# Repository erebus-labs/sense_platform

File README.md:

sense-platform
==============
#Sensor Platform 
+ *Title:* A low-cost,  low-power sensor platform with modular sensor addition and base station reprogramming/configuration
+ *Project Short Name:* Open Sensor Platform
+ *Sponsors:* 
  + [Dr. Mike Borowczak](https://www.linkedin.com/in/mborowczak) @ [Erebus Labs](http://www.erebuslabs.com)
  + [Dr. Andrea Burrows] (http://uwyo.academia.edu/AndreaBurrows) @ [University of Wyoming](http://www.uwyo.edu/seced/faculty-staff/andrea-burrows.html)
+ *Senior Design Team:* 
    + Colten Nye
    + Steve Pierce
    + Golriz Sedaghat
+ *PSU Academic Advisor:* [Dr. Lisa Zurk](http://web.cecs.pdx.edu/~zurkl/) 
+ *Targeted Users:* K-20 students (and families/communities) who want to know about their environment 

## Problem/Task
Current sensor platforms are either completed closed source and expensive or partially open, non-customizable, and trivial. The task at hand is to build a fully contained sensor platform / collection device for $25-$50 USD for at volume runs (development versions would be higher with short PCB runs).  The sensor platform must include the ability to add both sensors (physical components) as well as custom code in an intuitive (GUI?) programming environment.

##Background
Current hardware sensor solutions either require programming/electronics experience beyond the reach of many K12 (K20) students, parents, teachers and faculty – or they so turn-key that there is little to no “STEM” required to get a solution up and running. Furthermore, there are currently no “build it yourself” approaches to sensor design. The closest existing solutions revolve around the Arduino platform – though the short coming here is again the abstraction of many of the details as well as the barrier of entry for most K12 students, parents, faculty – especially in mid-large scale deployments in a classroom or a school (>30-1000 units).

In 2013/2014 a first revision Proof of Concept was developed and implemented – this can be used as a starting point once preliminary design investigation has concluded.

##Skill Requirements (Order of importance):
+ embedded System Design {Architecture, Programming}
+ Platform Agnostic Program Development (e.g. crossplatform or web UI)
+ PCB Layout and Design
+	Communication (BT, Serial, wifi?) 

##Other Details: 
+	IP Ownership: Joint/”none”: The goal is to release an open hardware device and software; joint ownership of the original design, publicly available for reuse under similar attribution
+	Extension after End of Project: 50-100 parts run to distribute to high-needs schools as a mechanism to enhance/drive STEM as a college degree option.
+	Publication Opportunities: Conference and Journal Publication both in K20 Education, IEEE Spectrum, and/or others (joint ownership: ECE team and Sponsors) [resume/CV builder!]
+	No NDA required. 

##Requirements (Wish List): **THIS SECTION SHOULD BE REPLACED BY PSU TEAM BEFORE DESIGN START**

###Must Have
+ [ ]	Low hardware cost <$50 per unit
+ [ ]	Open Source Hardware Design & Board (can use “closed source” components: ASICs, uC, etc.)
  + [ ]	Must Have a Multi-Chip solution – e.g. no single SoC; split data store
+ [ ]	Open Software Repository (github)
+ [ ]	Built-in basic sensor array (Oxygen, VoC, Accelerometer) + Ability to add at least one sensor
+ [ ]	Power:
  + [ ]	Low power operation (3 month duty-cycle; minimum 12 measurements per hour +sync)
  + [ ] Built in power source / power pack
+ [ ]	External Device Tethering/Sync upon physical request
+ [ ] Parameterized data collection mechanism
  + [ ] Set sensor Upper and Lower Thresholds
  + [ ] Polling frequency
  + [ ] Measurement to Physical Value Translation (they’re not all linear)
+ [ ] Set of units for each team member and two sponsors

###Like to Have
+ [ ]	Hardware cost <$30 per unit
+ [ ]	High Humidity Operation
+ [ ]	Swappable, Muxable Sensor array +software support
+ [ ]	Power
  + [ ] Ultra-low power operation (6 month duty-cycle; minimum 12 measurements per hour +sync)
  + [ ] Built in rechargeable power source / power pack
+ [ ] Device Tethering/Sync through Bluetooth/wifi in-range
+ [ ] High Level API wrapper to control device functionality for novice programmers
+ [ ] Partnership building with a local K-12 school; Flexible options include teacher conversations, lesson development, and/or helping with a lesson stemming from this research
+ [ ] Set of units for each team member and two sponsors + 5 extra units

###Nice to Have
+ [ ] Hardware cost <$15 per unit
+ [ ] GUI based overlay for API suitable for use by K-8 students
+ [ ] Power
  + [ ] Extremely-low power operation (12 month duty-cycle; minimum 12 measurements per hour +sync)
  + [ ] Built in power source w/solar recharge
+ [ ] Set of units for each team member and two sponsors + 10 extra units (5 to sponsors; 5 to PSU)

##Milestones:

###Hardware Evaluation to satisfy given constraints 
+ [ ] Main System: Modification of existing Open Hardware Design to create part or creation of custom PCB?
+ [ ] Power System: Battery capacity + recharge + cycled usage + communication cost?
+ [ ] Communication mechanisms: Effective low cost communication and sync (without taxing power source)

###Implementation
+ [ ] Development of full hardware solution (can you detect VoCs > ~0.5 PPM)
+ [ ] Develop a [G]UI to [re]program and sync data to/from remote sensing board 
+ [ ] Development of power system
+ [ ] Development of communication system
+ [ ] Develop the Android/iOS/PC software for receiving sync data, database/cloud upload, visualization

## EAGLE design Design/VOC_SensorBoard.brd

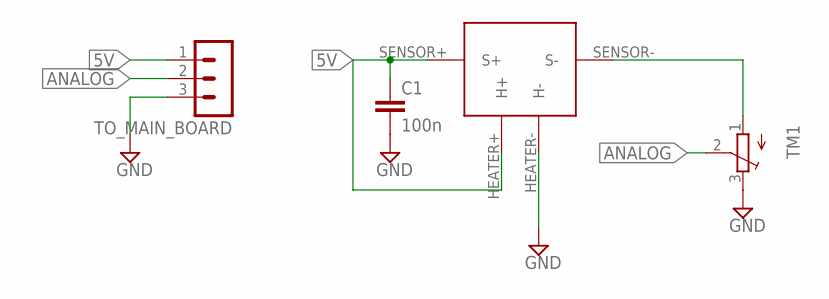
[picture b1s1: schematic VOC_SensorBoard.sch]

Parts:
C1: 100n; C0805
TM1: TRIMPOTTC33X; TC33X
TO_MAIN_BOARD: MA03-1
U$1: TGS2602

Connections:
5V: C1.1, TO_MAIN_BOARD.1, U$1.HEATER+ (H+), U$1.SENSOR+ (S+)
ANALOG: TM1.2 (S), TO_MAIN_BOARD.2
GND: C1.2, TM1.3 (E), TO_MAIN_BOARD.3, U$1.HEATER- (H-)
unnamed: TM1.1 (A), U$1.SENSOR- (S-)

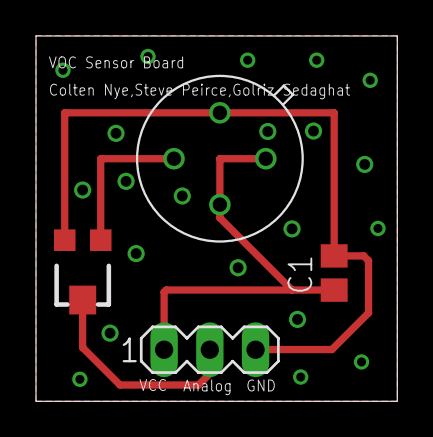
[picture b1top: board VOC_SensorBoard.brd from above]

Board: 2 copper layers, 20.1 x 20.3 mm, 4 parts (0 on the bottom side), 4 nets.

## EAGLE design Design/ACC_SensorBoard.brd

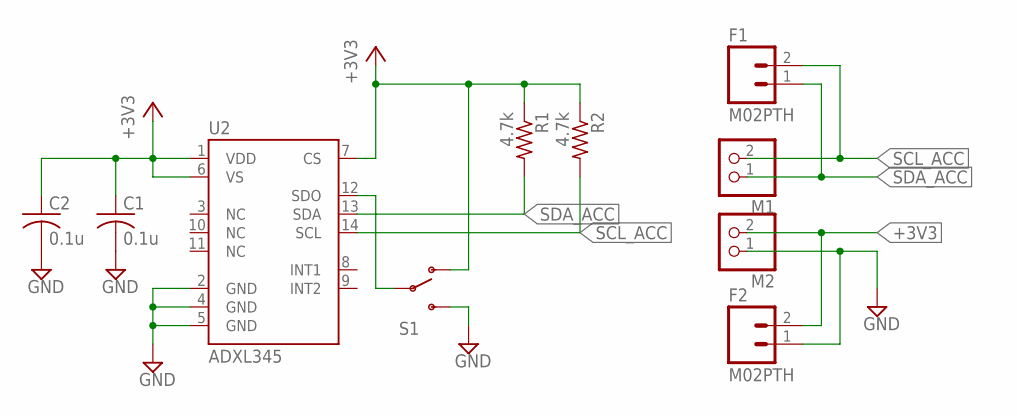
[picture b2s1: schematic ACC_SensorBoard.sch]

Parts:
C1, C2: 0.1u; C0805
F1, F2: M02PTH; 1X02
M1, M2: PINHD-1X2; 1X02
R1, R2: 4.7k; R0805
S1: SWITCH-SPDTSMD; AYZ0202
U2: ADXL345; LGA14

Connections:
+3V3: C1.1, C2.1, F2.2, M2.2, R1.1, R2.1, S1.1 (O), U2.1 (VDD), U2.6 (VS), U2.7 (CS)
GND: C1.2, C2.2, F2.1, M2.1, S1.3 (S), U2.2 (GND), U2.4 (GND), U2.5 (GND)
unnamed: S1.2, U2.12 (SDO)
SCL_ACC: F1.2, M1.2, R2.2, U2.14 (SCL)
SDA_ACC: F1.1, M1.1, R1.2, U2.13 (SDA)

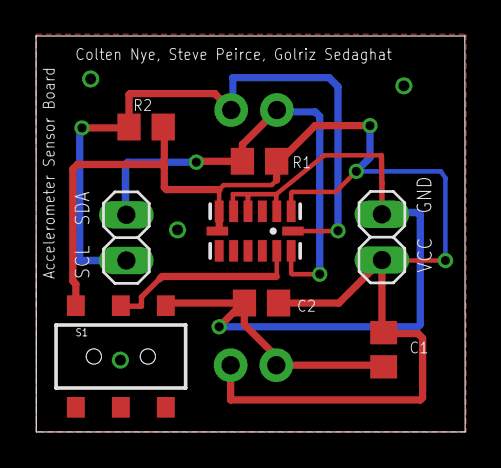
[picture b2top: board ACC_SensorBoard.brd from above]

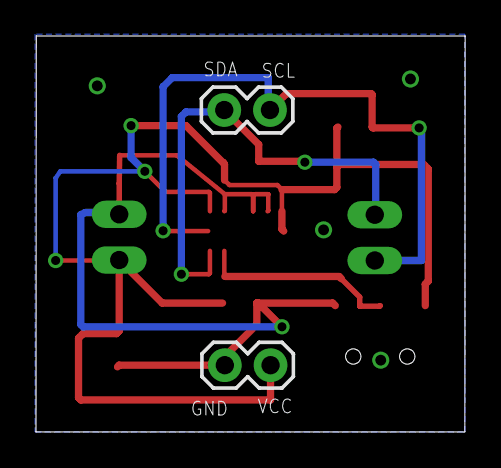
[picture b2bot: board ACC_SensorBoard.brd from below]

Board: 2 copper layers, 23.8 x 22.0 mm, 10 parts (2 on the bottom side), 5 nets.

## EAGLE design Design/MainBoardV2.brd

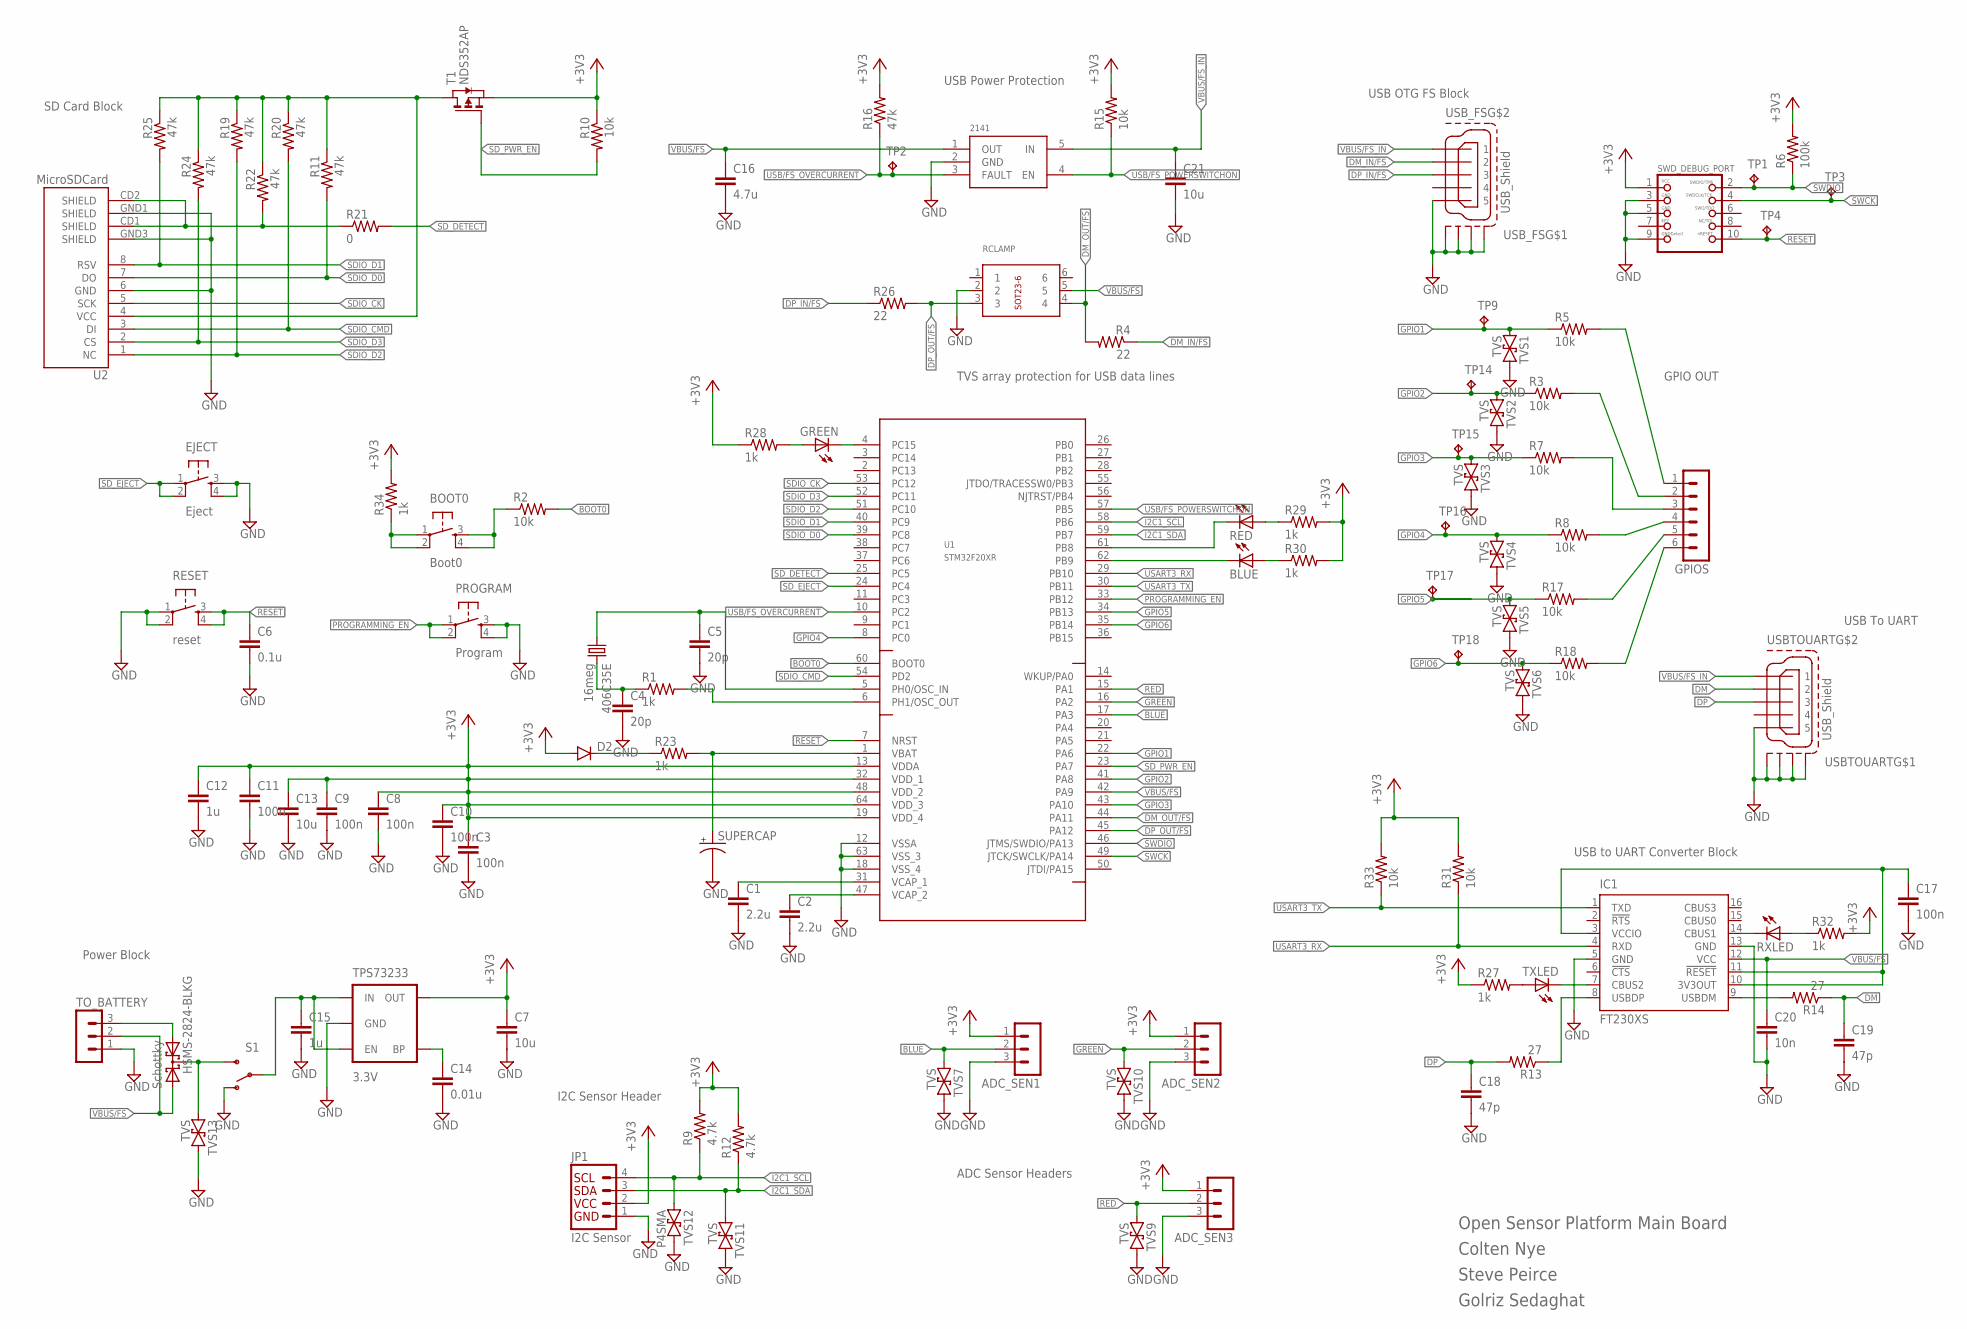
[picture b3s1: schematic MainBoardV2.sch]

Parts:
406C35E: 16meg; CTS406
2141: NCP1400A_STEPUP; SOT23-5
ADC_SEN1, ADC_SEN2, ADC_SEN3: MA03-1
BLUE: LEDSML0805; SML0805
BOOT0: Boot0; TACTILE-SWITCH-SMD
C1, C2: 2.2u; C0805
C3, C8, C9, C10, C11, C17: 100n; C0805
C4, C5: 20p; C0805
C6: 0.1u; C0805
C7, C13, C21: 10u; C0805
C12, C15: 1u; C0805
C14: 0.01u; C0805
C16: 4.7u; C0805
C18, C19: 47p; C0805
C20: 10n; C0805
D2: DIODESMA; SMA-DIODE
EJECT: Eject; TACTILE-SWITCH-SMD
GPIOS: MA06-1
GREEN: LEDSML0805; SML0805
HSMS-2824-BLKG: Schottky; SOT23
IC1: FT230XS; SSOP16
JP1: I2C Sensor; 1X04
PROGRAM: Program; TACTILE-SWITCH-SMD
R1, R23, R27, R28, R29, R30, R32, R34: 1k; R0805
R2, R3, R5, R7, R8, R10, R15, R17, R18, R31, R33: 10k; R0805
R4, R26: 22; R0805
R6: 100k; R0805
R9, R12: 4.7k; R0805
R11, R16, R19, R20, R22, R24, R25: 47k; R0805
R13, R14: 27; R0805
R21: 0; R0805
RCLAMP: BREAKOUT_SOT23-6
RED: LEDSML0805; SML0805
RESET: reset; TACTILE-SWITCH-SMD
RXLED: LEDSML0805; SML0805
S1: SWITCH-SPDTSMD; AYZ0202
SUPERCAP: SUPERCAP; 414-VA5R
SWD_DEBUG_PORT: JTAG-CORTEXM3; 2X05_1.27MM_SMT
T1: NDS352AP; SOT-23
TO_BATTERY: MA03-1
TP1, TP2, TP3, TP4, TP9, TP14, TP15, TP16, TP17, TP18: TPB1,27; B1,27
TPS73233: 3.3V; SOT23-5
TVS1, TVS2, TVS3, TVS4, TVS5, TVS6, TVS7, TVS9, TVS10, TVS11, TVS13: TVS; SMA-DIODE
TVS12: P4SMA; SMA-DIODE
TXLED: LEDSML0805; SML0805
U1: STM32F20XR; LQFP64
U2: MicroSDCard; MICRO-SD-SOCKET-PP
USBTOUART: USB_Shield; ZX62R-B-5P
USB_FS: USB_Shield; ZX62R-B-5P

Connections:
+3V3: ADC_SEN1.1, ADC_SEN2.1, ADC_SEN3.1, C3.1, C7.1, C8.1, C9.1, C10.1, C11.1, C12.1, C13.1, D2.A, JP1.2, R6.2, R9.2, R10.1, R12.2, R15.2, R16.2, R27.1, R28.1, R29.2, R30.2, R31.2, R32.2, R33.2, R34.2, SWD_DEBUG_PORT.1, T1.2 (S), TPS73233.5 (OUT), U1.13 (VDDA), U1.19 (VDD_4), U1.32 (VDD_1), U1.48 (VDD_2), U1.64 (VDD_3)
BLUE: ADC_SEN1.2, TVS7.A (1), U1.17 (PA3)
BOOT0: R2.2, U1.60 (BOOT0)
DEBUG_LED/NP1: GPIOS.1, R5.2
DEBUG_LED/NP2: GPIOS.2, R3.2
DEBUG_LED/NP3: GPIOS.3, R7.2
DEBUG_LED/NP4: GPIOS.4, R8.2
DEBUG_LED/NP5: GPIOS.5, R17.2
DEBUG_LED/NP6: GPIOS.6, R18.2
DM: C19.1, R14.1, USBTOUART.2
DM_IN/FS: R4.1, USB_FS.2
DM_OUT/FS: R4.2, RCLAMP.4, U1.44 (PA11)
DP: C18.1, R13.2, USBTOUART.3
DP_IN/FS: R26.1, USB_FS.3
DP_OUT/FS: R26.2, RCLAMP.3, U1.45 (PA12)
GND: 2141.2 (GND), ADC_SEN1.3, ADC_SEN2.3, ADC_SEN3.3, C1.2, C2.2, C3.2, C4.2, C5.2, C6.2, C7.2, C8.2, C9.2, C10.2, C11.2, C12.2, C13.2, C14.2, C15.2, C16.2, C17.2, C18.2, C19.2, C20.2, C21.2, EJECT.3, EJECT.4, IC1.5 (GND), IC1.13 (GND), JP1.1, PROGRAM.3, PROGRAM.4, RCLAMP.2, RESET.1, RESET.2, S1.1 (O), SUPERCAP.-, SWD_DEBUG_PORT.3, SWD_DEBUG_PORT.5, SWD_DEBUG_PORT.9, TO_BATTERY.1, TPS73233.2 (GND), TVS1.C (2), TVS2.C (2), TVS3.C (2), TVS4.C (2), TVS5.C (2), TVS6.C (2), TVS7.C (2), TVS9.C (2), TVS10.C (2), TVS11.C (2), TVS12.C (2), TVS13.C (2), U1.12 (VSSA), U1.18 (VSS_4), U1.63 (VSS_3), U2.6 (GND), U2.GND1 (SHIELD), U2.GND3 (SHIELD), USBTOUART.5, USBTOUART.M1 (S1), USBTOUART.M2 (S2), USBTOUART.M3 (S3), USBTOUART.M4 (S4), USB_FS.5, USB_FS.M1 (S1), USB_FS.M2 (S2), USB_FS.M3 (S3), USB_FS.M4 (S4)
GPIO1: R5.1, TP9.TP, TVS1.A (1), U1.22 (PA6)
GPIO2: R3.1, TP14.TP, TVS2.A (1), U1.41 (PA8)
GPIO3: R7.1, TP15.TP, TVS3.A (1), U1.43 (PA10)
GPIO4: R8.1, TP16.TP, TVS4.A (1), U1.8 (PC0)
GPIO5: R17.1, TP17.TP, TVS5.A (1), U1.34 (PB13)
GPIO6: R18.1, TP18.TP, TVS6.A (1), U1.35 (PB14)
GREEN: ADC_SEN2.2, TVS10.A (1), U1.16 (PA2)
I2C1_SCL: JP1.4, R9.1, TVS12.A (1), U1.58 (PB6)
I2C1_SDA: JP1.3, R12.1, TVS11.A (1), U1.59 (PB7)
unnamed: C1.1, U1.31 (VCAP_1)
unnamed: C2.1, U1.47 (VCAP_2)
unnamed: GREEN.C, U1.4 (PC15)
unnamed: HSMS-2824-BLKG.1 (A1), TO_BATTERY.3
unnamed: 406C35E.3 (2), C4.1, R1.1
unnamed: BOOT0.3, BOOT0.4, R2.1
unnamed: C17.1, IC1.3 (VCCIO), IC1.10 (3V3OUT), IC1.11 (!RESET)
unnamed: IC1.9 (USBDM), R14.2
unnamed: IC1.8 (USBDP), R13.1
unnamed: C14.1, TPS73233.4 (BP)
unnamed: BOOT0.1, BOOT0.2, R34.1
unnamed: R27.2, TXLED.A
unnamed: BLUE.C, U1.62 (PB9)
unnamed: R21.1, R22.2, U2.CD1 (SHIELD), U2.CD2 (SHIELD)
unnamed: D2.C, R23.1
unnamed: R29.1, RED.A
unnamed: GREEN.A, R28.2
unnamed: BLUE.A, R30.1
unnamed: R32.1, RXLED.A
unnamed: RED.C, U1.61 (PB8)
unnamed: HSMS-2824-BLKG.3 (C), S1.3 (S), TVS13.A (1)
unnamed: IC1.14 (CBUS1), RXLED.C
unnamed: IC1.7 (CBUS2), TXLED.C
unnamed: R11.1, R19.1, R20.1, R22.1, R24.1, R25.1, T1.1 (D), U2.4 (VCC)
OSC_IN: 406C35E.1, C5.1, U1.5 (PH0/OSC_IN)
OSC_OUT: R1.2, U1.6 (PH1/OSC_OUT)
PROGRAMMING_EN: PROGRAM.1, PROGRAM.2, U1.33 (PB12)
RED: ADC_SEN3.2, TVS9.A (1), U1.15 (PA1)
RESET: C6.1, RESET.3, RESET.4, SWD_DEBUG_PORT.10, TP4.TP, U1.7 (NRST)
SDIO_CK: U1.53 (PC12), U2.5 (SCK)
SDIO_CMD: R20.2, U1.54 (PD2), U2.3 (DI)
SDIO_D0: R11.2, U1.39 (PC8), U2.7 (DO)
SDIO_D1: R25.2, U1.40 (PC9), U2.8 (RSV)
SDIO_D2: R19.2, U1.51 (PC10), U2.1 (NC)
SDIO_D3: R24.2, U1.52 (PC11), U2.2 (CS)
SD_DETECT: R21.2, U1.25 (PC5)
SD_EJECT: EJECT.1, EJECT.2, U1.24 (PC4)
SD_PWR_EN: R10.2, T1.3 (G), U1.23 (PA7)
SWCK: SWD_DEBUG_PORT.4, TP3.TP, U1.49 (JTCK/SWCLK/PA14)
SWDIO: R6.1, SWD_DEBUG_PORT.2, TP1.TP, U1.46 (JTMS/SWDIO/PA13)
USART3_RX: IC1.4 (RXD), R31.1, U1.29 (PB10)
USART3_TX: IC1.1 (TXD), R33.1, U1.30 (PB11)
USB/FS_OVERCURRENT: 2141.3 (FAULT), R16.1, TP2.TP, U1.10 (PC2)
USB/FS_POWERSWITCHON: 2141.4 (EN), R15.1, U1.57 (PB5)
VBAT: R23.2, SUPERCAP.+, U1.1 (VBAT)
VBUS/FS: 2141.1 (OUT), C16.1, C20.1, HSMS-2824-BLKG.2 (A2), IC1.12 (VCC), RCLAMP.5, TO_BATTERY.2, U1.42 (PA9)
VBUS/FS_IN: 2141.5 (IN), C21.1, USBTOUART.1, USB_FS.1
VIN: C15.1, S1.2, TPS73233.1 (IN), TPS73233.3 (EN)

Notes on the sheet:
Colten Nye
USB OTG FS Block
I2C Sensor Header
ADC Sensor Headers
SD Card Block
Power Block
Steve Peirce
Golriz Sedaghat
Open Sensor Platform Main Board
GPIO OUT
USB to UART Converter Block
USB Power Protection
TVS array protection for USB data lines
USB To UART

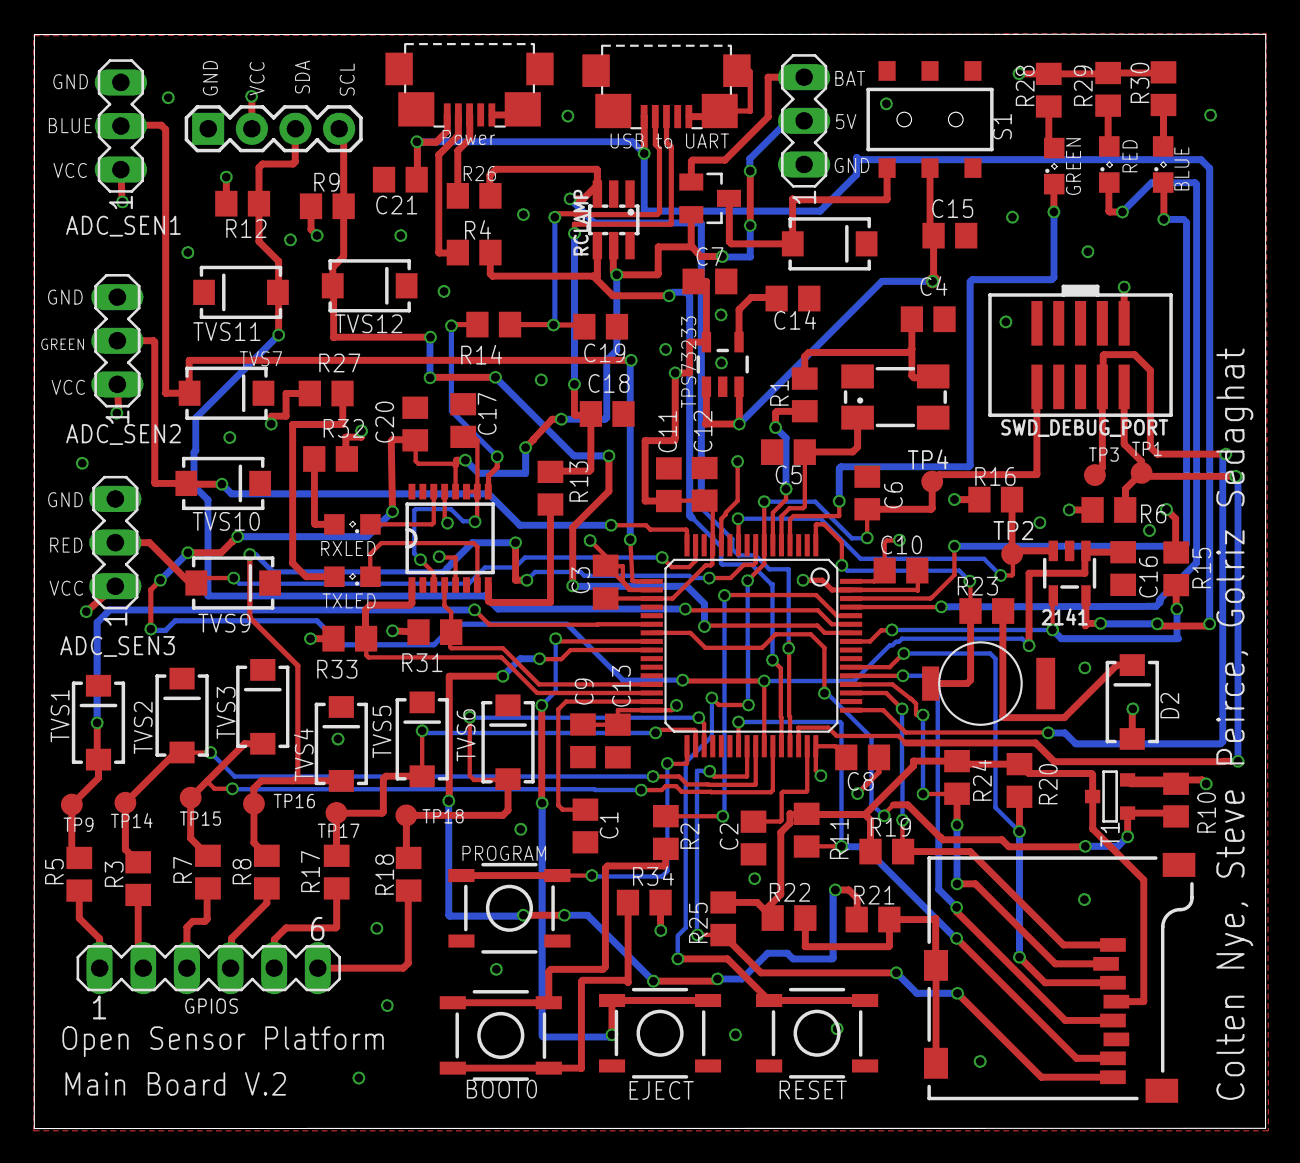
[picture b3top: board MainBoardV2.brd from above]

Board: 4 copper layers, 71.7 x 63.7 mm, 107 parts (0 on the bottom side), 73 nets.

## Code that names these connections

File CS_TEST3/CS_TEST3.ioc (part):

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Mcu.Name=STM32F207V(C-E-F-G)Tx
Mcu.Package=LQFP100
Mcu.UserName=STM32F207VCTx
PA0-WKUP.Signal=ADCx_IN0
PA1.Signal=ADCx_IN1
PA10.Mode=OTG/Dual_Role_Device
PA10.Signal=USB_OTG_FS_ID
PA11.Mode=OTG/Dual_Role_Device
PA11.Signal=USB_OTG_FS_DM
PA12.Mode=OTG/Dual_Role_Device
PA12.Signal=USB_OTG_FS_DP
PA13.Mode=JTAG(4-pin)
PA13.Signal=SYS_JTMS-SWDIO
PA14.Mode=JTAG(4-pin)
PA14.Signal=SYS_JTCK-SWCLK
PA15.Mode=JTAG(4-pin)
PA15.Signal=SYS_JTDI
PA2.Signal=ADCx_IN2
PA3.Signal=ADCx_IN3
PA4.Signal=ADCx_IN4
PA5.Mode=TX_Only_Simplex_Unidirect_Master
PA5.Signal=SPI1_SCK
PA7.Mode=TX_Only_Simplex_Unidirect_Master
PA7.Signal=SPI1_MOSI
PA8.Mode=Activate_SOF_FS
PA8.Signal=USB_OTG_FS_SOF
PB10.Mode=I2C
PB10.Signal=I2C2_SCL
PB11.Mode=I2C
PB11.Signal=I2C2_SDA
PB13.GPIOParameters=GPIO_PuPd,GPIO_Mode
PB13.GPIO_Mode=GPIO_MODE_INPUT
PB13.GPIO_PuPd=GPIO_PULLUP
PB13.Signal=GPIO_Input
PB14.GPIOParameters=GPIO_PuPd,GPIO_Mode
PB14.GPIO_Mode=GPIO_MODE_INPUT
PB14.GPIO_PuPd=GPIO_PULLUP
PB14.Signal=GPIO_Input
PB15.GPIOParameters=GPIO_PuPd,GPIO_Mode
PB15.GPIO_Mode=GPIO_MODE_INPUT
PB15.GPIO_PuPd=GPIO_PULLUP
PB15.Signal=GPIO_Input
PB3.Mode=JTAG(4-pin)
PB3.Signal=SYS_JTDO-SWO
PB6.Mode=I2C
PB6.Signal=I2C1_SCL
PB7.Mode=I2C
PB7.Signal=I2C1_SDA
PC10.Mode=SD_4_bits_Wide_bus
PC10.Signal=SDIO_D2
PC11.Mode=SD_4_bits_Wide_bus
PC11.Signal=SDIO_D3
PC12.Mode=SD_4_bits_Wide_bus
PC12.Signal=SDIO_CK
PC14-OSC32_IN.Mode=LSE-External-Oscillator
PC14-OSC32_IN.Signal=RCC_OSC32_IN
PC15-OSC32_OUT.Mode=LSE-External-Oscillator
PC15-OSC32_OUT.Signal=RCC_OSC32_OUT
PC8.Mode=SD_4_bits_Wide_bus
PC8.Signal=SDIO_D0
PC9.Mode=SD_4_bits_Wide_bus
PC9.Signal=SDIO_D1
PD2.Mode=SD_4_bits_Wide_bus
PD2.Signal=SDIO_CMD
PD8.GPIOParameters=GPIO_ModeDefaultOutputPP,GPIO_Speed,GPIO_PuPd
PD8.GPIO_ModeDefaultOutputPP=GPIO_MODE_OUTPUT_PP
PD8.GPIO_PuPd=GPIO_NOPULL
PD8.GPIO_Speed=GPIO_SPEED_LOW
PD8.Signal=GPIO_Output
PE10.GPIOParameters=GPIO_ModeDefaultOutputPP,GPIO_Speed,GPIO_PuPd
PE10.GPIO_ModeDefaultOutputPP=GPIO_MODE_OUTPUT_OD
PE10.GPIO_PuPd=GPIO_NOPULL
PE10.GPIO_Speed=GPIO_SPEED_LOW
PE10.Signal=GPIO_Output
PE7.GPIOParameters=GPIO_ModeDefaultOutputPP,GPIO_Speed,GPIO_PuPd
PE7.GPIO_ModeDefaultOutputPP=GPIO_MODE_OUTPUT_OD
PE7.GPIO_PuPd=GPIO_NOPULL
PE7.GPIO_Speed=GPIO_SPEED_LOW
PE7.Signal=GPIO_Output
PE8.GPIOParameters=GPIO_ModeDefaultOutputPP,GPIO_Speed,GPIO_PuPd
PE8.GPIO_ModeDefaultOutputPP=GPIO_MODE_OUTPUT_OD
PE8.GPIO_PuPd=GPIO_PULLUP
PE8.GPIO_Speed=GPIO_SPEED_LOW
PE8.Signal=GPIO_Output
PE9.GPIOParameters=GPIO_ModeDefaultOutputPP,GPIO_Speed,GPIO_PuPd
PE9.GPIO_ModeDefaultOutputPP=GPIO_MODE_OUTPUT_OD
PE9.GPIO_PuPd=GPIO_PULLUP
PE9.GPIO_Speed=GPIO_SPEED_LOW
PE9.Signal=GPIO_Output
PH0-OSC_IN.Mode=HSE-External-Clock-Source
PH0-OSC_IN.Signal=RCC_OSC_IN
PH1-OSC_OUT.Mode=HSE-External-Clock-Source
PH1-OSC_OUT.Signal=RCC_OSC_OUT
RCC.HSE_VALUE=25000000
RCC.SYSCLKSource=RCC_SYSCLKSOURCE_HSE

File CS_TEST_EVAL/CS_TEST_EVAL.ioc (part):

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Mcu.Name=STM32F207I(C-E-F-G)Hx
Mcu.Package=UFBGA176
Mcu.UserName=STM32F207IGHx
PA0-WKUP.Signal=ADCx_IN0
PA1.Signal=ADCx_IN1
PA10.Mode=OTG/Dual_Role_Device
PA10.Signal=USB_OTG_FS_ID
PA11.Mode=OTG/Dual_Role_Device
PA11.Signal=USB_OTG_FS_DM
PA12.Mode=OTG/Dual_Role_Device
PA12.Signal=USB_OTG_FS_DP
PA2.Signal=ADCx_IN2
PA3.Signal=ADCx_IN3
PA8.Signal=S_TIM1_CH1
PA9.Mode=Activate_VBUS
PA9.Signal=USB_OTG_FS_VBUS
PB3.Mode=Full_Duplex_Master
PB3.Signal=SPI1_SCK
PB4.Mode=Full_Duplex_Master
PB4.Signal=SPI1_MISO
PB5.Mode=Full_Duplex_Master
PB5.Signal=SPI1_MOSI
PC10.Mode=SD_4_bits_Wide_bus
PC10.Signal=SDIO_D2
PC11.Mode=SD_4_bits_Wide_bus
PC11.Signal=SDIO_D3
PC12.Mode=SD_4_bits_Wide_bus
PC12.Signal=SDIO_CK
PC13.Mode=Calibration_512Hz
PC13.Signal=RTC_AF1
PC8.Mode=SD_4_bits_Wide_bus
PC8.Signal=SDIO_D0
PC9.Mode=SD_4_bits_Wide_bus
PC9.Signal=SDIO_D1
PD2.Mode=SD_4_bits_Wide_bus
PD2.Signal=SDIO_CMD
PE10.Signal=GPIO_Input
PE12.Signal=GPIO_Output
PF0.Mode=I2C
PF0.Signal=I2C2_SDA
PF1.Mode=I2C
PF1.Signal=I2C2_SCL
PH0-OSC_IN.Mode=HSE-External-Oscillator
PH0-OSC_IN.Signal=RCC_OSC_IN
PH1-OSC_OUT.Mode=HSE-External-Oscillator
PH1-OSC_OUT.Signal=RCC_OSC_OUT
PH7.Mode=I2C
PH7.Signal=I2C3_SCL
PH8.Mode=I2C
PH8.Signal=I2C3_SDA
RCC.HSE_VALUE=25000000
RCC.SYSCLKFreq_VALUE=30000000
RCC.SYSCLKSource=RCC_SYSCLKSOURCE_PLLCLK

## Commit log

2014-11-11 Polluting README.md
    For now - just a replication of the initial proposal document.
2014-11-11 Minor edits to README.md
2014-11-23 Create gh-pages branch via GitHub
2014-11-27 Typographical corrections
    Corrected Pierce's Last Name and an internal link.
2014-12-07 Modifications to README.md
    The requirements section is cleaned up in terms of some markup issues; the entire section should be redone by the PSU Team before design work begins.
2015-01-10 Documentation for the STM32F207VCT6
2015-01-12 WeeklyProgressReport1
2015-01-20 WeeklyProgressReport2
2015-01-20 ProjectProposal
2015-01-24 Reference Manual, Primary Document!
2015-01-24 initial jtag script via OpenOCD
2015-02-04 Created WPR directory
2015-02-07 Added WPR templates directory
    corrected typo in a template
2015-02-10 Revert "Added WPR templates directory"
    This reverts commit 010b1c3c8af00644d52bd70e62520bace0251321.
2015-02-16 WPRs
2015-02-16 Revert "Revert "Added WPR templates directory""
    This reverts commit 5f586f43dbf15a03a260b0fdc3fc161b8b85ecb3.
2015-02-16 Revert the Revert !
2015-02-16 remove unneccessary WPR fragments
2015-02-20 requirements
2015-02-20 proposal outline
2015-02-21 Flowchart diagrams for programming the devicee
2015-02-23 Formal Requirements
2015-02-23 Mockups and file restructure
2015-02-23 Test Plan
2015-02-24 Documents
2015-02-24 D Makefile for STM32 using STMCube LHAL Libraries.
2015-02-24 Documents 2
2015-02-24 show golriz
2015-02-24 prop outline
2015-02-24 Small Corrections
2015-02-24 D D Receipt for Dev board from DigilKey
2015-02-24 raw code test, GPIOE
2015-02-24 CAPSTONE Test Program v3 from STMCubeMX, ALL Libraries needed
2015-02-24 D Programming
2015-02-24 Header files for STM32f205/7
2015-02-25 Documents for eval board
2015-02-25 Example USB HID Chrome APP
2015-02-25 Added credit to former associate, although completely revised
2015-02-26 current code for new eval board w all libs
2015-02-26 added GPIO blink
2015-02-26 GPIO tests
2015-02-26 TRUEstudio project
2015-02-26 upload
2015-02-27 Notes from proposal
2015-02-27 Started Proposal Revision
2015-02-28 Schematic Update
2015-02-28 Document Revision
2015-03-01 Revert "Document Revision"
    This reverts commit 87a539b43a6471277175cce403c1623fabaade23.
2015-03-01 SchematicRevision
2015-03-01 ChangeTheBlockName
2015-03-03 Proposal update
2015-03-03 rename STM DOCS
2015-03-18 Design Updates
2015-03-19 chrome app
2015-03-19 Updated schematics and boards
2015-03-19 Updates
    - Main board diagram was revised
    - Proposal document was completed
    - Project schedule was revised
2015-03-19 Pin list update
2015-03-19 About to add feature
    loading filetypes from file
2015-03-19 working on writing to file
2015-03-19 more on proposal
2015-03-20 FIRMWARE BACKUPS
    temporary backups of firmware files
2015-03-20 FIRMWARE BACKUPS
    backup of accelerometer header
2015-03-22 Design Final Revision
2015-03-23 VOC was taken off from the BOM
2015-03-24 Slight changes
2015-03-28 Test Plan Overview OpenOffice version (*.odt)
2015-03-28 Test Plan Overview MS Word version (*.docx)
2015-03-29 Restructure Docs dir, Add GUI compare table
    renamed "Project Flow Docs" to simply "Documents"
    removed "Project Documents" Subdirectory
    Added "Meeting Notes" directory
    Added GUI platform comparison table
2015-04-08 Misc updates
2015-04-15 Create main_41515.c
    Curent version being worked on, still based on STM207 until all systems are live. MISSING: USART RX and SDIO functions
2015-04-16 Current working version
2015-04-16 Current working version. Needs SDIO and continuing work on USART RX. Serial will program timers and fill sensor struct
2015-04-16 Updated error on USART RX IRQ callback routine
2015-04-17 Work on config parsing
2015-04-17 Revised Test Plan
2015-04-17 Changed the location
2015-04-17 Project Schedule Revision
2015-04-17 Project schedule PDF
2015-04-20 STMCube Project
2015-04-20 Updated Pin List
2015-04-20 ModNextVersion
2015-04-24 trying to get windows version of git to work
2015-04-27 2nd Version of Board and Schematic
2015-04-30 Modified revision of board and schematic
2015-05-07 Preliminary Poster
2015-05-07 STD Lib implementation, USART3 TX working, remainder templated
2015-05-07 Poster
2015-05-07 Serial Protocol
    look in .\Config Protocol\serialParser\serialParser\SerialParser.cpp
2015-05-07 Added I2C config, ADC config, etc.
2015-05-08 Added http to address in readme
2015-05-10 Create STD_PERIPH_TEMPLATE
2015-05-10 STDPeriphLib Template project
2015-05-12 HAL LIb Project
2015-05-21 Updated Pinlist
2015-06-08 Extra file deleted
2015-06-09 Updating/Cleaning-up documents
2015-06-14 Final Report
2015-06-14 User's Manual

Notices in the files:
parts and their libraries:
SparkFun-Sensors: Licensing: Creative Commons ShareAlike 4.0 International - https://creativecommons.org/licenses/by-sa/4.0
microbuilder: This work is placed in the public domain, and may be freely used for commercial and non-commercial work with the following conditions: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
